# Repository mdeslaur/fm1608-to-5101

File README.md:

# FM1608 to 5101 ram adapter

This is a small adapter board to use inexpensive DIP FM1608 FRAM memory
chip in games that require a 5101 static ram to save ram contents during
power off so a battery is no longer required.

For example, it can be used in Midway Omega Race or Williams Defender.

A 74HCT00 ic is required to handle the 5101's dual chip enable lines.

This design has been tested in a Defender, and appears to work well.

Gerbers, BOM, and other files to get the boards fabricated by JLCPCB are
located in the production directory.

A PDF of the schematic, and some 3d rendering images are in the docs
directory.

Change history:  
2024-12-29 - 1.0 - Initial version  

To Do:  
- test in Omega Race

Marc Deslauriers

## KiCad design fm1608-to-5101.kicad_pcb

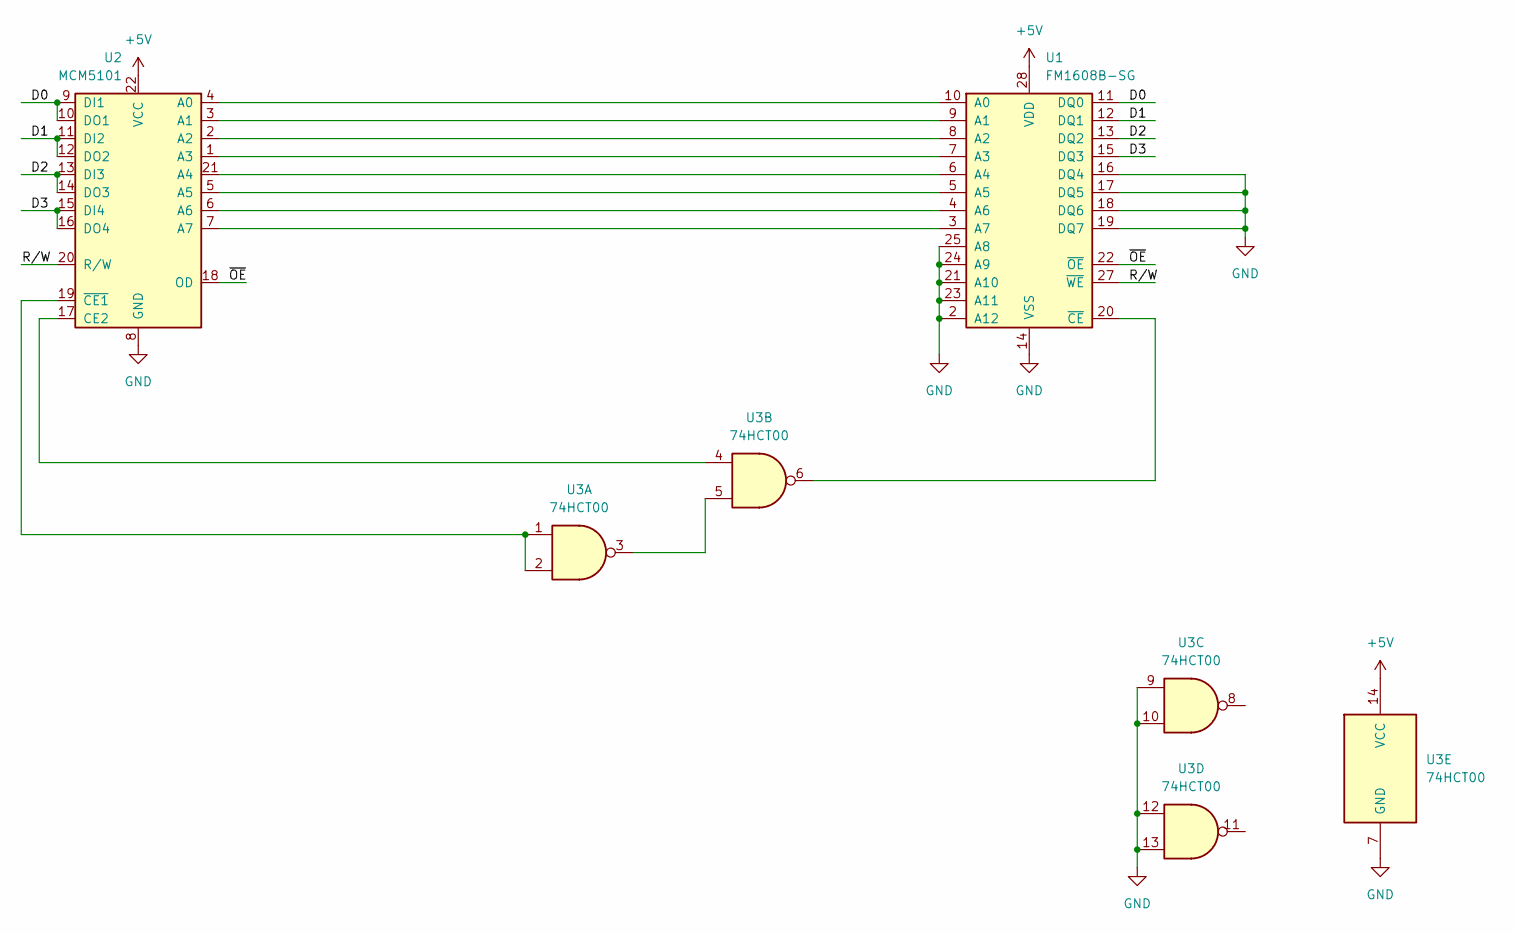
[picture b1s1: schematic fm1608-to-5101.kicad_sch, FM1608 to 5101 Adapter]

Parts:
U1: FM1608B-SG; DIP-28_W15.24mm_Socket_LongPads
U2: MCM5101; DIP-22_W10.16mm_Socket_LongPads
U3: 74HCT00; SOIC-14_3.9x8.7mm_P1.27mm; LCSC Part # C6764

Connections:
+5V: U1.28 (VDD), U2.22 (VCC), U3.14 (VCC)
/D0: U1.11 (DQ0), U2.9 (DI1), U2.10 (DO1)
/D1: U1.12 (DQ1), U2.11 (DI2), U2.12 (DO2)
/D2: U1.13 (DQ2), U2.13 (DI3), U2.14 (DO3)
/D3: U1.15 (DQ3), U2.15 (DI4), U2.16 (DO4)
/R/W: U1.27 (~WE), U2.20 (R/W)
/~OE: U1.22 (~OE), U2.18 (OD)
GND: U1.2 (A12), U1.14 (VSS), U1.16 (DQ4), U1.17 (DQ5), U1.18 (DQ6), U1.19 (DQ7), U1.21 (A10), U1.23 (A11), U1.24 (A9), U1.25 (A8), U2.8 (GND), U3.7 (GND), U3.9, U3.10, U3.12, U3.13
unnamed: U1.10 (A0), U2.4 (A0)
unnamed: U1.9 (A1), U2.3 (A1)
unnamed: U1.8 (A2), U2.2 (A2)
unnamed: U1.7 (A3), U2.1 (A3)
unnamed: U1.6 (A4), U2.21 (A4)
unnamed: U1.5 (A5), U2.5 (A5)
unnamed: U1.4 (A6), U2.6 (A6)
unnamed: U1.3 (A7), U2.7 (A7)
unnamed: U1.20 (~CE), U3.6
unnamed: U2.17 (CE2), U3.4
unnamed: U2.19 (~CE1), U3.1, U3.2
unnamed: U3.3, U3.5

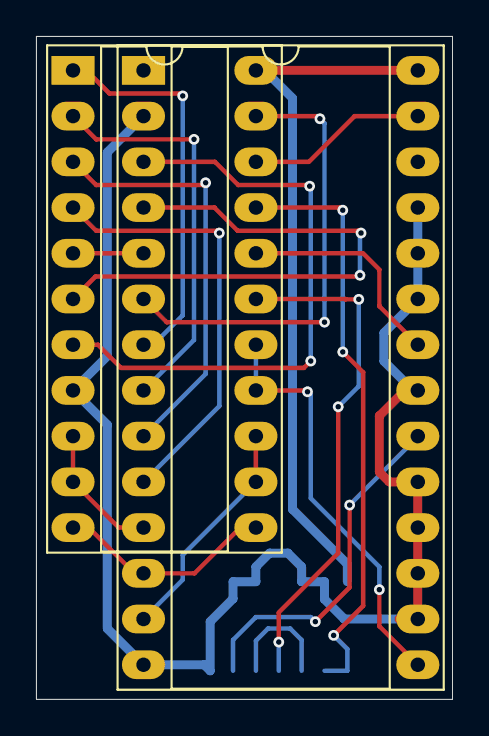
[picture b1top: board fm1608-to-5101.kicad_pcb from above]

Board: 2 copper layers, 23.1 x 36.8 mm, 3 parts (1 on the bottom side), 20 nets.

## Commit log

2024-12-29 README.md: fix typo
2024-12-29 .gitignore: fix directory name
2024-12-29 remove backup files from git repo
2024-12-29 added schematic pdf and 3d renderings to docs directory
2025-01-20 updated README.md to add defender testing
